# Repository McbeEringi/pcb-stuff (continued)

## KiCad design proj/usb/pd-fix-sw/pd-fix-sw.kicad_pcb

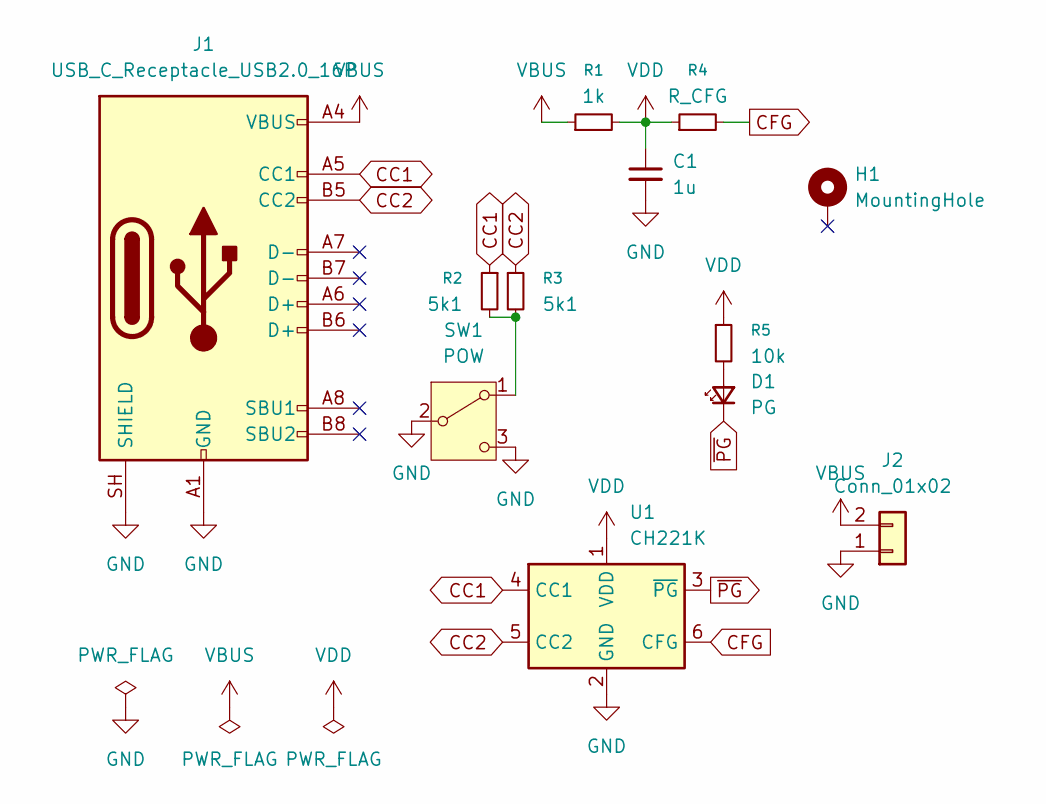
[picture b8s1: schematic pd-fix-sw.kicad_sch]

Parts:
C1: 1u; C_0603_1608Metric
D1: PG; LED_0603_1608Metric
H1: MountingHole; MountingHole_3.2mm_M3_Pad_TopOnly
J1: USB_C_Receptacle_USB2.0_16P; USB_C_Receptacle_GCT_USB4105-xx-A_16P_TopMnt_Horizontal
J2: Conn_01x02; JST_XH_S2B-XH-A_1x02_P2.50mm_Horizontal
R1: 1k; R_0603_1608Metric
R2, R3: 5k1; R_0603_1608Metric
R4: R_CFG; R_0603_1608Metric
R5: 10k; R_0603_1608Metric
SW1: POW; IS-1245T-G
U1: CH221K; SOT-23-6

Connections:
CC1: J1.A5 (CC1), R2.1, U1.4 (CC1)
CC2: J1.B5 (CC2), R3.1, U1.5 (CC2)
CFG: R4.2, U1.6 (CFG)
GND: C1.2, J1.A1 (GND), J1.A12 (GND), J1.B1 (GND), J1.B12 (GND), J1.SH (SHIELD), J2.1, SW1.2 (B), SW1.3 (C), U1.2 (GND)
unnamed: D1.2 (A), R5.2
unnamed: R2.2, R3.2, SW1.1 (A)
VBUS: J1.A4 (VBUS), J1.A9 (VBUS), J1.B4 (VBUS), J1.B9 (VBUS), J2.2, R1.1
VDD: C1.1, R1.2, R4.1, R5.1, U1.1 (VDD)
~PG: D1.1 (K), U1.3 (~PG)

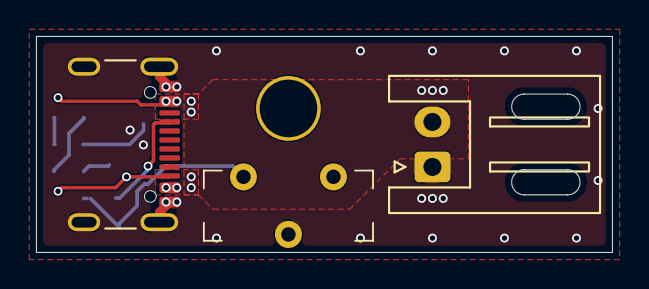
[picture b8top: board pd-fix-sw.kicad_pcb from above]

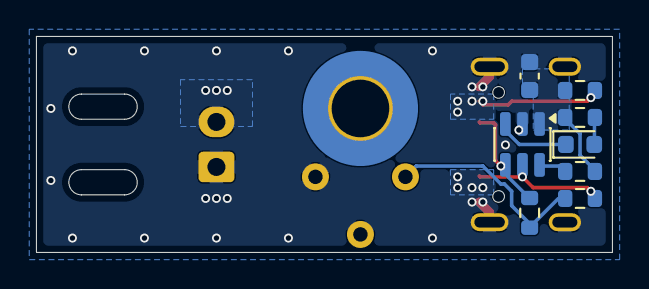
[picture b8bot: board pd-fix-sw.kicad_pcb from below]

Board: 2 copper layers, 32.0 x 12.0 mm, 12 parts (9 on the bottom side), 9 nets.

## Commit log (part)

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2024-03-01 おい！！！！！！！！！！！！！！！
2024-08-31 tx04_updi_fix
2024-08-31 mx09_updi_fix
2024-12-09 tx04_re
2024-12-09 polish
2024-12-10 7seg
